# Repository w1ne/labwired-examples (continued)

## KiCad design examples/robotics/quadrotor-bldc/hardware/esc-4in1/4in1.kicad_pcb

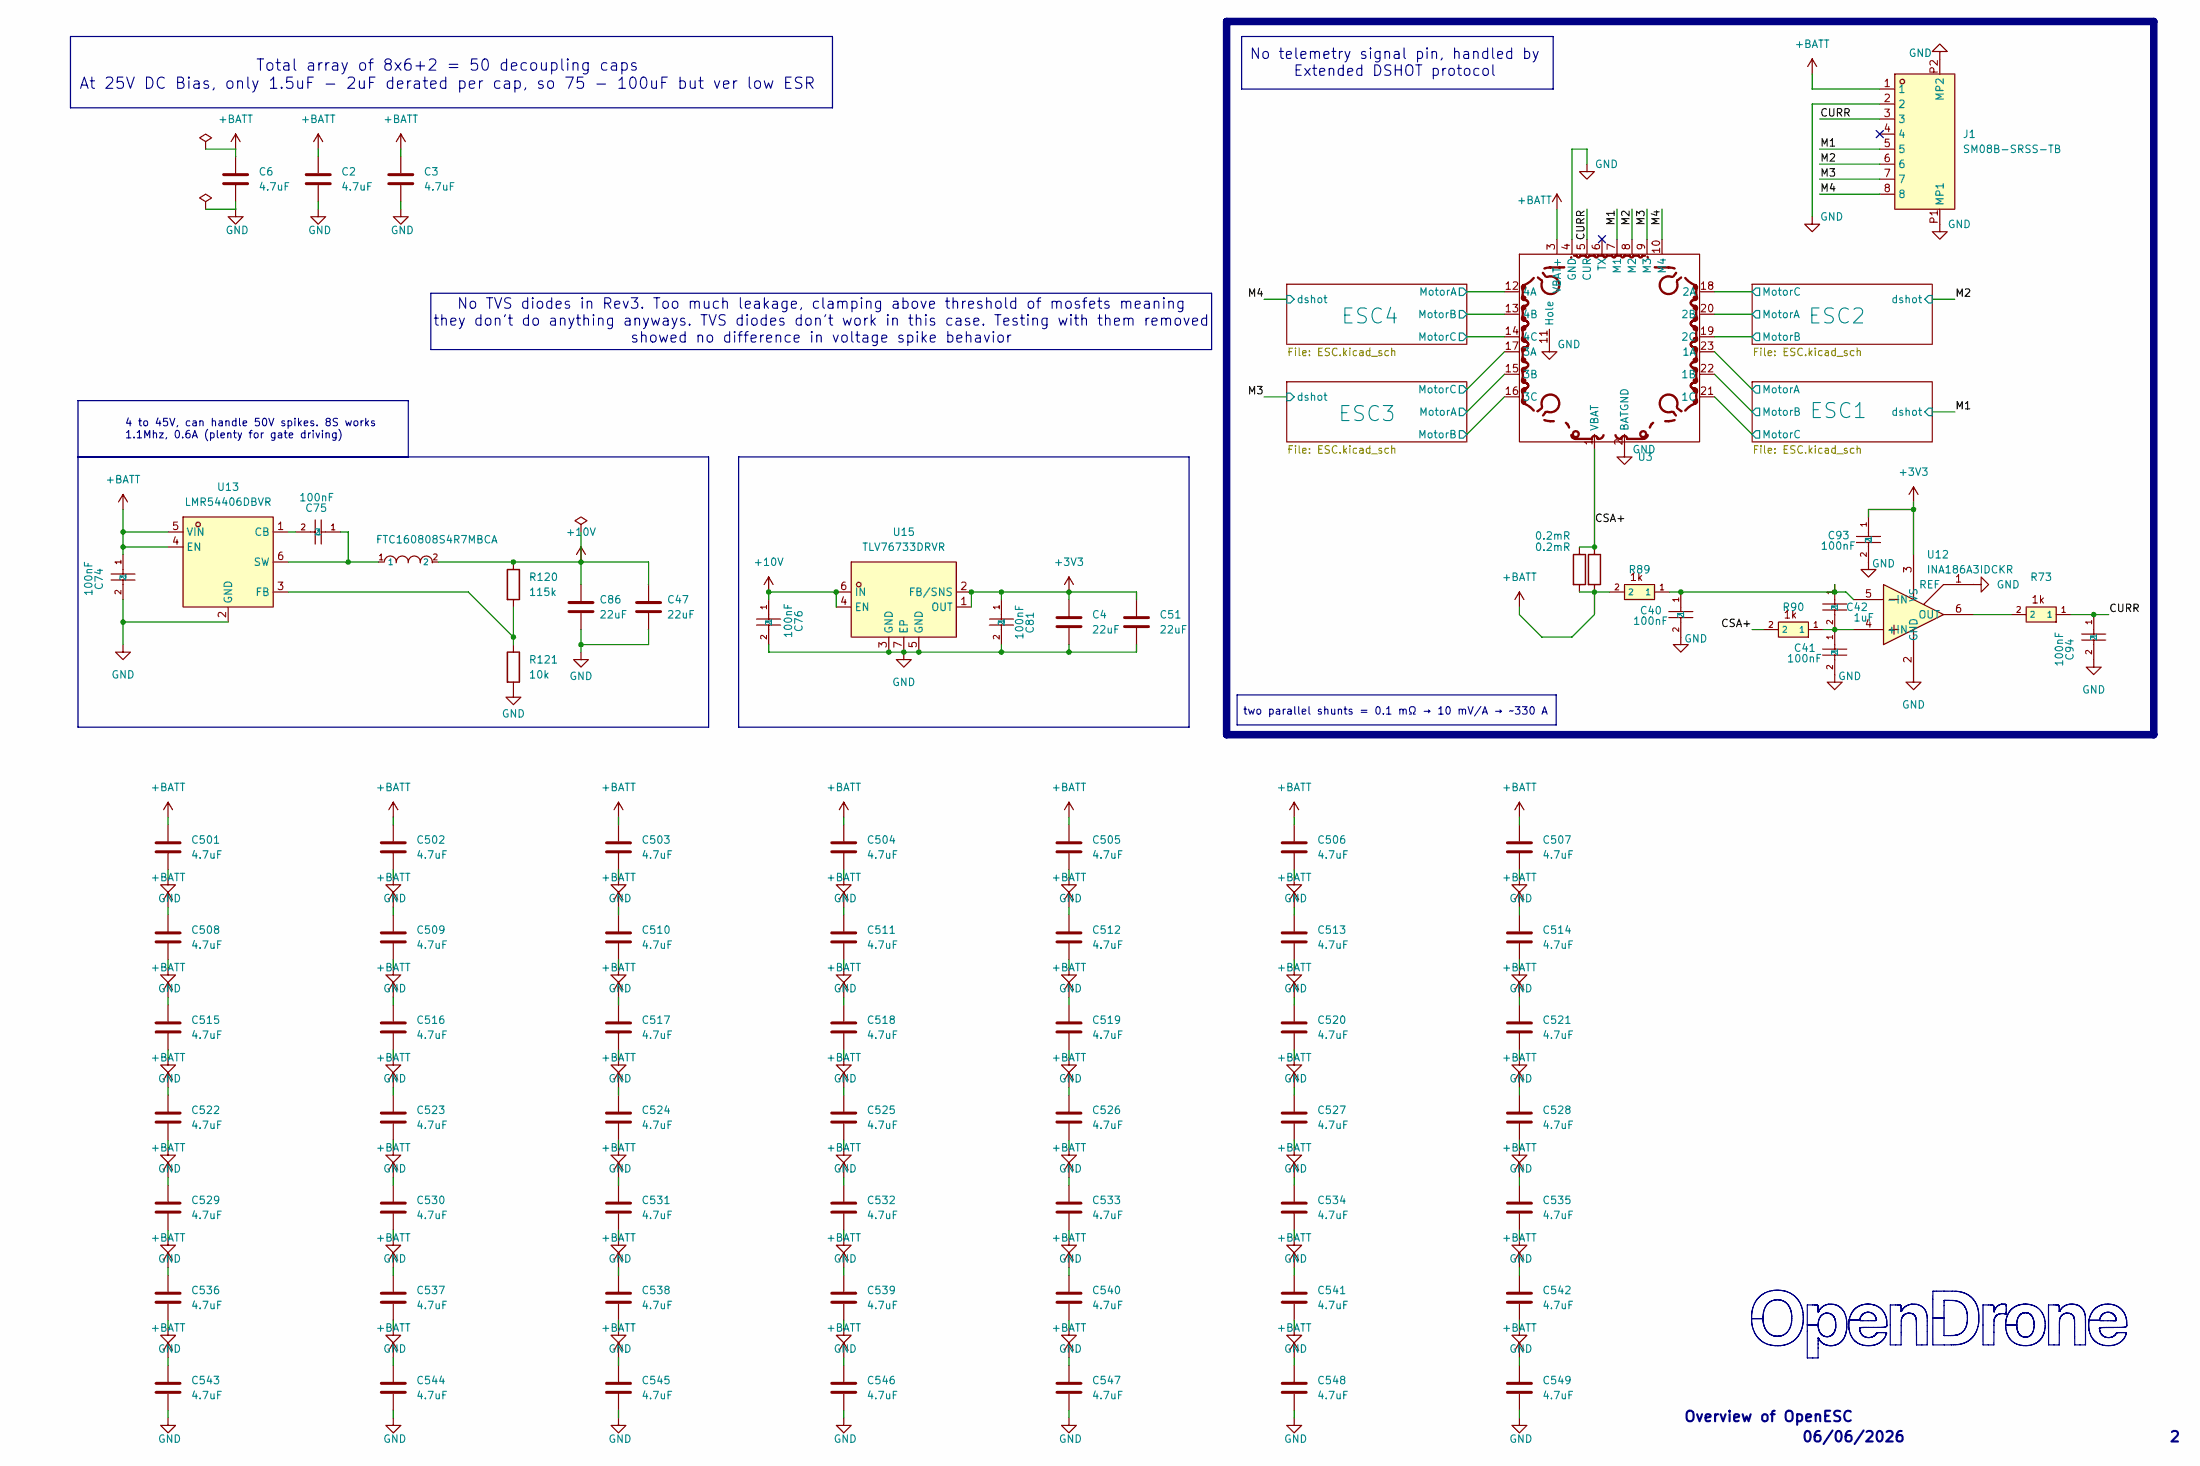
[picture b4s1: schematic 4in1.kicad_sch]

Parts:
C2, C3, C6, C501, C502, C503, C504, C505, C506, C507, C508, C509, C510, C511, C512, C513, C514, C515, C516, C517, C518, C519, C520, C521, C522, C523, C524, C525, C526, C527, C528, C529, C530, C531, C532, C533, C534, C535, C536, C537, C538, C539, C540, C541, C542, C543, C544, C545, C546, C547, C548, C549: 4.7uF; C_1206_3216Metric; MPN TCC1206X7R475K500HT; LCSC C380366
C4, C51: 22uF; C_0402_1005Metric; MPN CL05A226MQ5QUNC; LCSC C105226
C40, C41: 100nF; C_0402_WIDE; MPN CL05B104KB54PNC; LCSC C307331
C42: 1uF; C_0402_1005Metric; MPN CC0402KRX7R6BB105; LCSC C7500381
C47, C86: 22uF; C_0603_1608Metric; MPN CL10A226MO7JZNC; LCSC C2762594
C74, C75, C76, C81, C93, C94: 100nF; C_0201_0603Metric; MPN GRM033R6YA104KE14D; LCSC C181043
J1: SM08B-SRSS-TB; JST_SM08B-SRSS-TB; MPN SM08B-SRSS-TB(LF)(SN); LCSC C160407
R73, R89, R90: 1k; C_0201_0603Metric; MPN 0201WMF1001TEE; LCSC C270365
R120: 115k; R_0201_0603Metric; MPN RTT011153FTH; LCSC C166378
R121: 10k; R_0201_0603Metric; MPN RC0201FR-0710KL; LCSC C106225
Rsense1, Rsense2: 0.2mR; R_2512_6332Metric; MPN ASR-S-3-0.2F; LCSC C695806
U3: 4in1ESC30x30
U12: INA186A3IDCKR; SOT-363_SC-70-6; MPN INA186A3IDCKR; LCSC C2058245
U13: LMR54406DBVR; SOT-23-6_L2.9-W1.6-P0.95-LS2.8-BR; MPN LMR54406DBVR; LCSC Part C5219316
U14: FTC160808S4R7MBCA; IND-SMD_L1.6-W0.8_FTC160865SR47MBCA; MPN FTC160808S4R7MBCA; LCSC C46594347
U15: TLV76733DRVR; WSON-6_L2.0-W2.0-P0.65-TL-EP; MPN TLV76733DRVR; LCSC C2848334

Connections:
+3V3: C4.2, C51.2, C81.1, C93.1, U12.3 (VS), U15.1 (OUT), U15.2 (FB/SNS); also elsewhere on the board
+10V: C47.1, C76.1, C86.1, R120.1, U14.2, U15.4 (EN), U15.6 (IN); also elsewhere on the board
+BATT: C2.1, C3.1, C6.1, C74.1, C501.1, C502.1, C503.1, C504.1, C505.1, C506.1, C507.1, C508.1, C509.1, C510.1, C511.1, C512.1, C513.1, C514.1, C515.1, C516.1, C517.1, C518.1, C519.1, C520.1, C521.1, C522.1, C523.1, C524.1, C525.1, C526.1, C527.1, C528.1, C529.1, C530.1, C531.1, C532.1, C533.1, C534.1, C535.1, C536.1, C537.1, C538.1, C539.1, C540.1, C541.1, C542.1, C543.1, C544.1, C545.1, C546.1, C547.1, C548.1, C549.1, J1.1, R89.2, Rsense1.2, Rsense2.2, U3.3 (VBAT+), U13.4 (EN), U13.5 (VIN); also elsewhere on the board
/CSA+: R90.2, Rsense1.1, Rsense2.1, U3.1 (VBAT)
/CURR: C94.1, J1.3, R73.1, U3.5 (CUR)
/ESC1/MotorA: U3.23 (1A); also elsewhere on the board
/ESC1/MotorB: U3.22 (1B); also elsewhere on the board
/ESC1/MotorC: U3.21 (1C); also elsewhere on the board
/ESC2/MotorA: U3.20 (2B); also elsewhere on the board
/ESC2/MotorB: U3.19 (2C); also elsewhere on the board
/ESC2/MotorC: U3.18 (2A); also elsewhere on the board
/ESC3/MotorA: U3.15 (3B); also elsewhere on the board
/ESC3/MotorB: U3.16 (3C); also elsewhere on the board
/ESC3/MotorC: U3.17 (3A); also elsewhere on the board
/ESC4/MotorA: U3.12 (4A); also elsewhere on the board
/ESC4/MotorB: U3.13 (4B); also elsewhere on the board
/ESC4/MotorC: U3.14 (4C); also elsewhere on the board
/M1: J1.5, U3.7 (M1); also elsewhere on the board
/M2: J1.6, U3.8 (M2); also elsewhere on the board
/M3: J1.7, U3.9 (M3); also elsewhere on the board
/M4: J1.8, U3.10 (M4); also elsewhere on the board
GND: C2.2, C3.2, C4.1, C6.2, C40.2, C41.2, C47.2, C51.1, C74.2, C76.2, C81.2, C86.2, C93.2, C94.2, C501.2, C502.2, C503.2, C504.2, C505.2, C506.2, C507.2, C508.2, C509.2, C510.2, C511.2, C512.2, C513.2, C514.2, C515.2, C516.2, C517.2, C518.2, C519.2, C520.2, C521.2, C522.2, C523.2, C524.2, C525.2, C526.2, C527.2, C528.2, C529.2, C530.2, C531.2, C532.2, C533.2, C534.2, C535.2, C536.2, C537.2, C538.2, C539.2, C540.2, C541.2, C542.2, C543.2, C544.2, C545.2, C546.2, C547.2, C548.2, C549.2, J1.2, J1.P1 (MP1), J1.P2 (MP2), R121.2, U3.2 (BATGND), U3.4 (GND), U3.11 (Hole), U12.1 (REF), U12.2 (GND), U13.2 (GND), U15.3 (GND), U15.5 (GND), U15.7 (EP); also elsewhere on the board
unnamed: C41.1, C42.2, R90.1, U12.4 (+IN)
unnamed: C40.1, C42.1, R89.1, U12.5 (-IN)
unnamed: R73.2, U12.6 (OUT)
unnamed: C75.2, U13.1 (CB)
unnamed: R120.2, R121.1, U13.3 (FB)
unnamed: C75.1, U13.6 (SW), U14.1

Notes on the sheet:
No telemetry signal pin, handled by Extended DSHOT protocol
Overview of OpenESC
No TVS diodes in Rev3. Too much leakage, clamping above threshold of mosfets meaning they don't do anything anyways. TVS diodes don't work in this case. Testing with them removed showed no difference in voltage spike behavior
06/06/2026
Total array of 8x6+2 = 50 decoupling caps At 25V DC Bias, only 1.5uF - 2uF derated per cap, so 75 - 100uF but ver low ESR
two parallel shunts = 0.1 mΩ → 10 mV/A → ~330 A
4 to 45V, can handle 50V spikes. 8S works 1.1Mhz, 0.6A (plenty for gate driving)

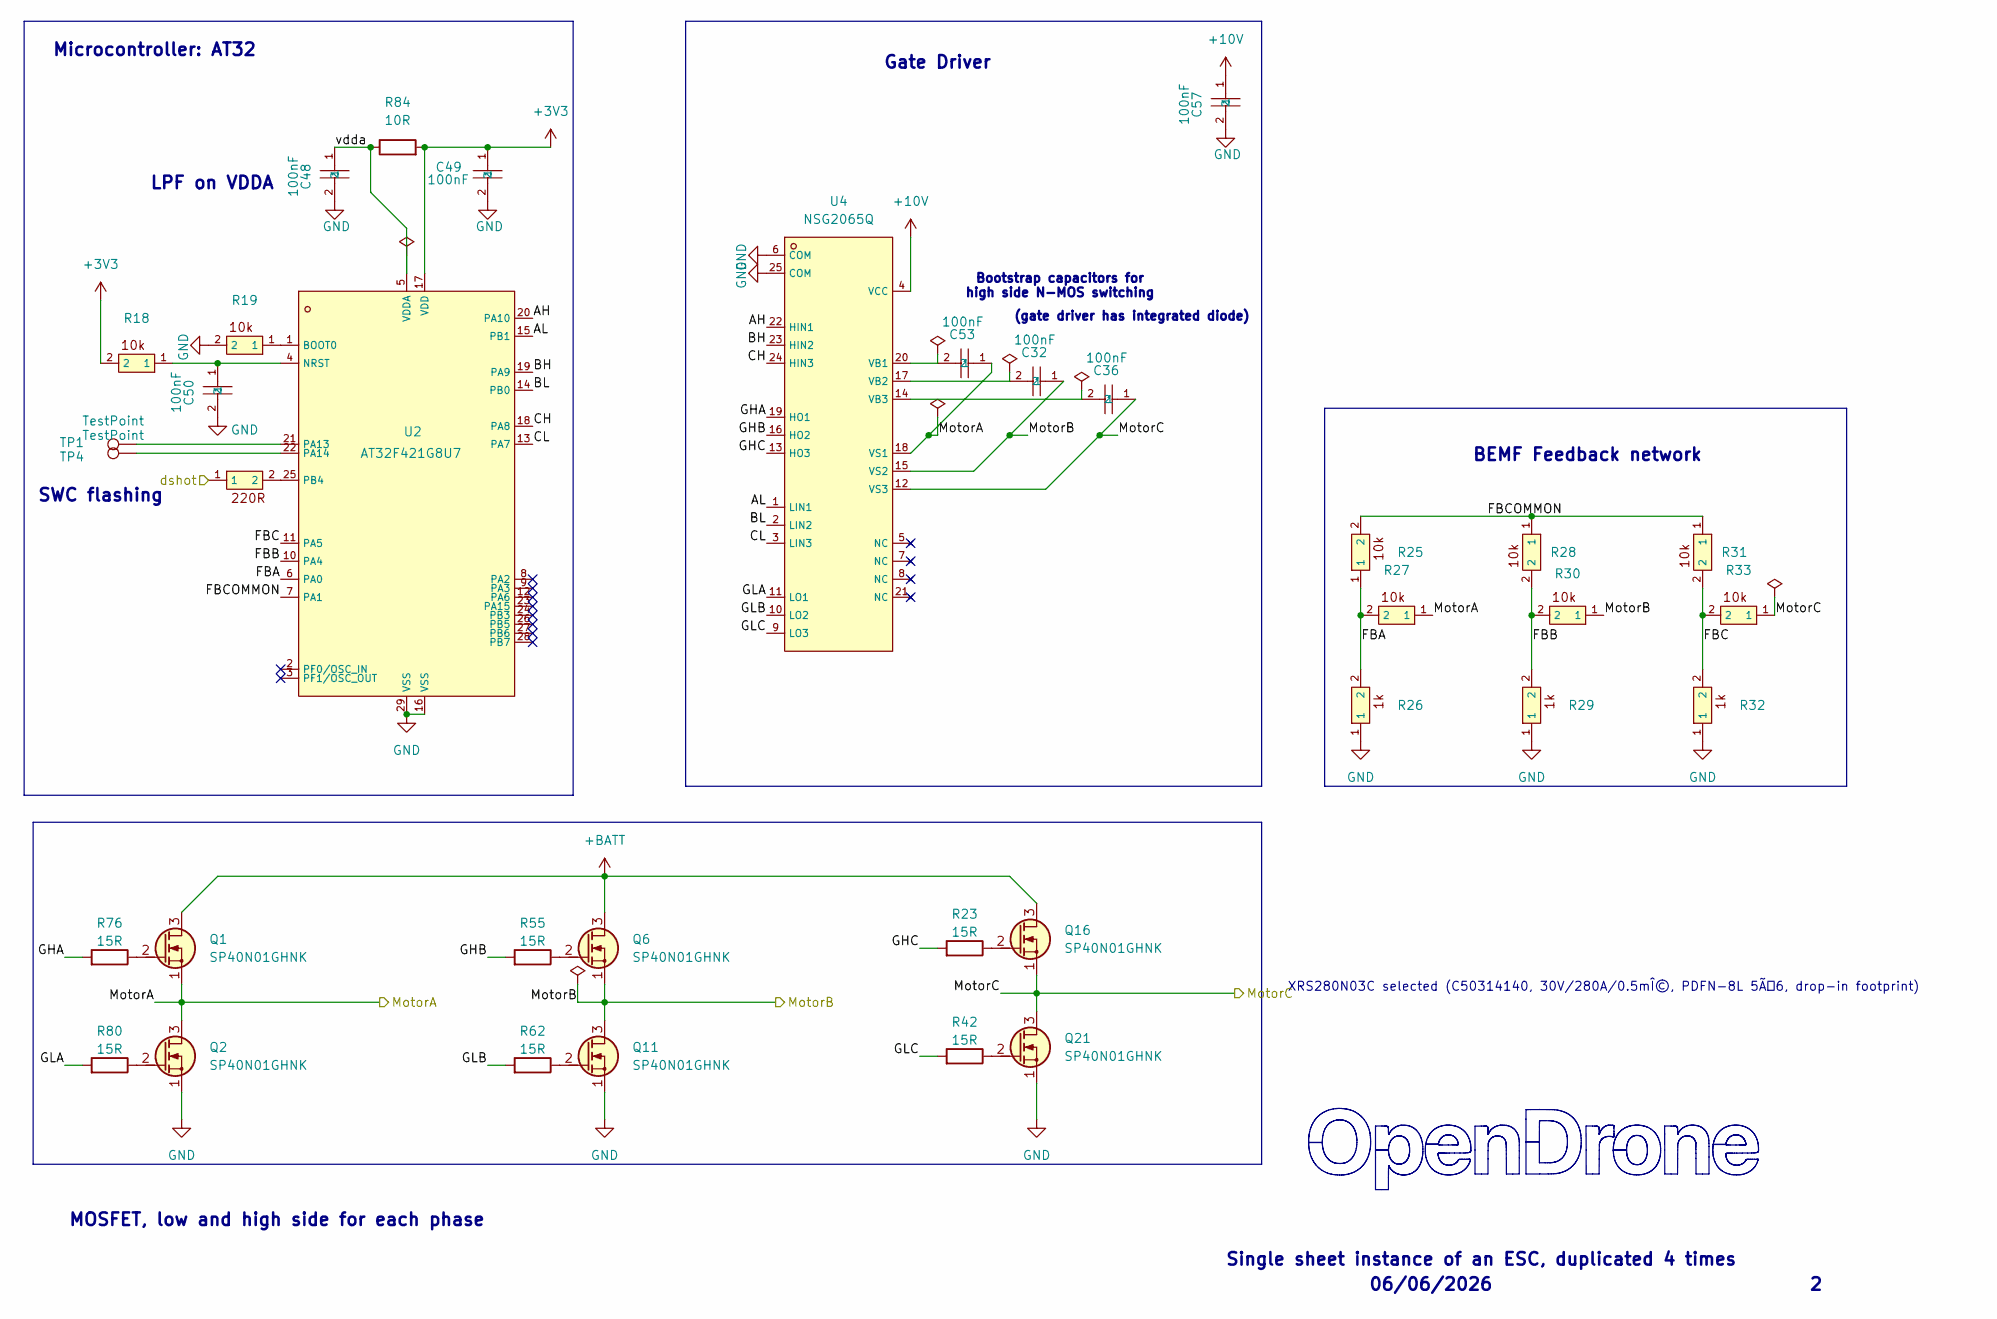
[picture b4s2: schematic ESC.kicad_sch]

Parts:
C32, C36, C53: 100nF; C_0402_WIDE; MPN CL05B104KB54PNC; LCSC C307331
C48, C49, C50, C57: 100nF; C_0201_0603Metric; MPN GRM033R6YA104KE14D; LCSC C181043
Q1, Q2, Q6, Q11, Q16, Q21: SP40N01GHNK; PDFN-8L_L6.0-W5.0-P1.27; MPN SP40N01GHNK; LCSC C22385416
R18, R19: 10k; R_0201_0603Metric; MPN RC0201FR-0710KL; LCSC C106225
R20: 220R; R_0201_0603Metric; MPN AC0201FR-07220RL; LCSC C226468
R23, R42, R55, R62, R76, R80: 15R; R_0201_0603Metric; MPN 0201WMF150JTEE; LCSC C473542
R25, R27, R28, R30, R31, R33: 10k; C_0201_0603Metric; MPN RC0201FR-0710KL; LCSC C106225
R26, R29, R32: 1k; C_0201_0603Metric; MPN 0201WMF1001TEE; LCSC C270365
R84: 10R; R_0201_0603Metric; MPN RC0201FR-0710RL; LCSC C106226
TP1, TP4: TestPoint; TestPoint_Pad_D1.0mm
U2: AT32F421G8U7; QFN-28_L4.0-W4.0-P0.40-TL-EP2.4; MPN AT32F421G8U7; LCSC C2765098
U4: NSG2065Q; QFN-24_L4.0-W4.0-P0.50-TL-EP2.8; MPN NSG2065Q; LCSC C41414478

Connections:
+3V3: C49.1, R18.2, R84.2, U2.17 (VDD); also elsewhere on the board
+10V: C57.1, U4.4 (VCC); also elsewhere on the board
+BATT: Q1.3 (D), Q6.3 (D), Q16.3 (D); also elsewhere on the board
/ESC1/AH: U2.20 (PA10), U4.22 (HIN1)
/ESC1/AL: U2.15 (PB1), U4.1 (LIN1)
/ESC1/BH: U2.19 (PA9), U4.23 (HIN2)
/ESC1/BL: U2.14 (PB0), U4.2 (LIN2)
/ESC1/CH: U2.18 (PA8), U4.24 (HIN3)
/ESC1/CL: U2.13 (PA7), U4.3 (LIN3)
/ESC1/FBA: R25.1, R26.2, R27.2, U2.6 (PA0)
/ESC1/FBB: R28.2, R29.2, R30.2, U2.10 (PA4)
/ESC1/FBC: R31.2, R32.2, R33.2, U2.11 (PA5)
/ESC1/FBCOMMON: R25.2, R28.1, R31.1, U2.7 (PA1)
/ESC1/GHA: R76.1, U4.19 (HO1)
/ESC1/GHB: R55.1, U4.16 (HO2)
/ESC1/GHC: R23.1, U4.13 (HO3)
/ESC1/GLA: R80.1, U4.11 (LO1)
/ESC1/GLB: R62.1, U4.10 (LO2)
/ESC1/GLC: R42.1, U4.9 (LO3)
/ESC1/MotorA: C53.1, Q1.1 (S), Q2.3 (D), R27.1, U4.18 (VS1); also elsewhere on the board
/ESC1/MotorB: C32.1, Q6.1 (S), Q11.3 (D), R30.1, U4.15 (VS2); also elsewhere on the board
/ESC1/MotorC: C36.1, Q16.1 (S), Q21.3 (D), R33.1, U4.12 (VS3); also elsewhere on the board
/ESC1/vdda: C48.1, R84.1, U2.5 (VDDA)
/M1: R20.1; also elsewhere on the board
GND: C48.2, C49.2, C50.2, C57.2, Q2.1 (S), Q11.1 (S), Q21.1 (S), R19.2, R26.1, R29.1, R32.1, U2.16 (VSS), U2.29 (VSS), U4.6 (COM), U4.25 (COM); also elsewhere on the board
unnamed: Q1.2 (G), R76.2
unnamed: Q2.2 (G), R80.2
unnamed: Q6.2 (G), R55.2
unnamed: Q11.2 (G), R62.2
unnamed: Q16.2 (G), R23.2
unnamed: Q21.2 (G), R42.2
unnamed: R19.1, U2.1 (BOOT0)
unnamed: C50.1, R18.1, U2.4 (NRST)
unnamed: TP1.1 (1_1), U2.21 (PA13)
unnamed: TP4.1 (1_1), U2.22 (PA14)
unnamed: R20.2, U2.25 (PB4)
unnamed: C53.2, U4.20 (VB1)
unnamed: C32.2, U4.17 (VB2)
unnamed: C36.2, U4.14 (VB3)

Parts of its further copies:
C33, C34, C35, C37, C38, C39, C56, C62, C67: 100nF; C_0402_WIDE; MPN CL05B104KB54PNC; LCSC C307331
C52, C54, C55, C58, C59, C60, C61, C63, C64, C65, C66, C68: 100nF; C_0201_0603Metric; MPN GRM033R6YA104KE14D; LCSC C181043
Q3, Q4, Q5, Q7, Q8, Q9, Q10, Q12, Q13, Q14, Q15, Q17, Q18, Q19, Q20, Q22, Q23, Q24: SP40N01GHNK; PDFN-8L_L6.0-W5.0-P1.27; MPN SP40N01GHNK; LCSC C22385416
R10, R12, R13, R15, R34, R36, R46, R48, R49, R51, R52, R54, R64, R66, R67, R69, R70, R72: 10k; C_0201_0603Metric; MPN RC0201FR-0710KL; LCSC C106225
R11, R14, R35, R47, R50, R53, R65, R68, R71: 1k; C_0201_0603Metric; MPN 0201WMF1001TEE; LCSC C270365
R21, R22, R40, R41, R58, R59: 10k; R_0201_0603Metric; MPN RC0201FR-0710KL; LCSC C106225
R24, R37, R38, R43, R44, R45, R56, R60, R61, R63, R74, R75, R77, R78, R79, R81, R82, R83: 15R; R_0201_0603Metric; MPN 0201WMF150JTEE; LCSC C473542
R39, R57, R87: 220R; R_0201_0603Metric; MPN AC0201FR-07220RL; LCSC C226468
R85, R86, R88: 10R; R_0201_0603Metric; MPN RC0201FR-0710RL; LCSC C106226
TP2, TP3, TP5, TP6, TP7, TP8: TestPoint; TestPoint_Pad_D1.0mm
U5, U7, U9: AT32F421G8U7; QFN-28_L4.0-W4.0-P0.40-TL-EP2.4; MPN AT32F421G8U7; LCSC C2765098
U6, U8, U10: NSG2065Q; QFN-24_L4.0-W4.0-P0.50-TL-EP2.8; MPN NSG2065Q; LCSC C41414478

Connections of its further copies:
+3V3: C55.1, C61.1, C66.1, R21.2, R40.2, R58.2, R85.2, R86.2, R88.2, U5.17 (VDD), U7.17 (VDD), U9.17 (VDD); also elsewhere on the board
+10V: C58.1, C63.1, C68.1, U6.4 (VCC), U8.4 (VCC), U10.4 (VCC); also elsewhere on the board
+BATT: Q7.3 (D), Q8.3 (D), Q9.3 (D), Q10.3 (D), Q13.3 (D), Q17.3 (D), Q18.3 (D), Q19.3 (D), Q20.3 (D); also elsewhere on the board
/ESC2/AH: U5.20 (PA10), U6.22 (HIN1)
/ESC2/AL: U5.15 (PB1), U6.1 (LIN1)
/ESC2/BH: U5.19 (PA9), U6.23 (HIN2)
/ESC2/BL: U5.14 (PB0), U6.2 (LIN2)
/ESC2/CH: U5.18 (PA8), U6.24 (HIN3)
/ESC2/CL: U5.13 (PA7), U6.3 (LIN3)
/ESC2/FBA: R10.1, R11.2, R12.2, U5.6 (PA0)
/ESC2/FBB: R13.2, R14.2, R15.2, U5.10 (PA4)
/ESC2/FBC: R34.2, R35.2, R36.2, U5.11 (PA5)
/ESC2/FBCOMMON: R10.2, R13.1, R34.1, U5.7 (PA1)
/ESC2/GHA: R77.1, U6.19 (HO1)
/ESC2/GHB: R56.1, U6.16 (HO2)
/ESC2/GHC: R24.1, U6.13 (HO3)
/ESC2/GLA: R81.1, U6.11 (LO1)
/ESC2/GLB: R63.1, U6.10 (LO2)
/ESC2/GLC: R43.1, U6.9 (LO3)
/ESC2/MotorA: C56.1, Q3.3 (D), Q7.1 (S), R12.1, U6.18 (VS1); also elsewhere on the board
/ESC2/MotorB: C33.1, Q8.1 (S), Q12.3 (D), R15.1, U6.15 (VS2); also elsewhere on the board
/ESC2/MotorC: C37.1, Q17.1 (S), Q22.3 (D), R36.1, U6.12 (VS3); also elsewhere on the board
/ESC2/vdda: C54.1, R85.1, U5.5 (VDDA)
/ESC3/AH: U7.20 (PA10), U8.22 (HIN1)
/ESC3/AL: U7.15 (PB1), U8.1 (LIN1)
/ESC3/BH: U7.19 (PA9), U8.23 (HIN2)
/ESC3/BL: U7.14 (PB0), U8.2 (LIN2)
/ESC3/CH: U7.18 (PA8), U8.24 (HIN3)
/ESC3/CL: U7.13 (PA7), U8.3 (LIN3)
/ESC3/FBA: R46.1, R47.2, R48.2, U7.6 (PA0)
/ESC3/FBB: R49.2, R50.2, R51.2, U7.10 (PA4)
/ESC3/FBC: R52.2, R53.2, R54.2, U7.11 (PA5)
/ESC3/FBCOMMON: R46.2, R49.1, R52.1, U7.7 (PA1)
/ESC3/GHA: R78.1, U8.19 (HO1)
/ESC3/GHB: R60.1, U8.16 (HO2)
/ESC3/GHC: R37.1, U8.13 (HO3)
/ESC3/GLA: R82.1, U8.11 (LO1)
/ESC3/GLB: R74.1, U8.10 (LO2)
/ESC3/GLC: R44.1, U8.9 (LO3)
/ESC3/MotorA: C62.1, Q4.3 (D), Q13.1 (S), R48.1, U8.18 (VS1); also elsewhere on the board
/ESC3/MotorB: C34.1, Q9.1 (S), Q14.3 (D), R51.1, U8.15 (VS2); also elsewhere on the board
/ESC3/MotorC: C38.1, Q18.1 (S), Q23.3 (D), R54.1, U8.12 (VS3); also elsewhere on the board
/ESC3/vdda: C60.1, R86.1, U7.5 (VDDA)
/ESC4/AH: U9.20 (PA10), U10.22 (HIN1)
/ESC4/AL: U9.15 (PB1), U10.1 (LIN1)
/ESC4/BH: U9.19 (PA9), U10.23 (HIN2)
/ESC4/BL: U9.14 (PB0), U10.2 (LIN2)
/ESC4/CH: U9.18 (PA8), U10.24 (HIN3)
/ESC4/CL: U9.13 (PA7), U10.3 (LIN3)
/ESC4/FBA: R64.1, R65.2, R66.2, U9.6 (PA0)
/ESC4/FBB: R67.2, R68.2, R69.2, U9.10 (PA4)
/ESC4/FBC: R70.2, R71.2, R72.2, U9.11 (PA5)
/ESC4/FBCOMMON: R64.2, R67.1, R70.1, U9.7 (PA1)
/ESC4/GHA: R79.1, U10.19 (HO1)
/ESC4/GHB: R61.1, U10.16 (HO2)
/ESC4/GHC: R38.1, U10.13 (HO3)
/ESC4/GLA: R83.1, U10.11 (LO1)
/ESC4/GLB: R75.1, U10.10 (LO2)
/ESC4/GLC: R45.1, U10.9 (LO3)
/ESC4/MotorA: C67.1, Q5.3 (D), Q19.1 (S), R66.1, U10.18 (VS1); also elsewhere on the board
/ESC4/MotorB: C35.1, Q10.1 (S), Q15.3 (D), R69.1, U10.15 (VS2); also elsewhere on the board
/ESC4/MotorC: C39.1, Q20.1 (S), Q24.3 (D), R72.1, U10.12 (VS3); also elsewhere on the board
/ESC4/vdda: C65.1, R88.1, U9.5 (VDDA)
/M2: R39.1; also elsewhere on the board
/M3: R57.1; also elsewhere on the board
/M4: R87.1; also elsewhere on the board
GND: C52.2, C54.2, C55.2, C58.2, C59.2, C60.2, C61.2, C63.2, C64.2, C65.2, C66.2, C68.2, Q3.1 (S), Q4.1 (S), Q5.1 (S), Q12.1 (S), Q14.1 (S), Q15.1 (S), Q22.1 (S), Q23.1 (S), Q24.1 (S), R11.1, R14.1, R22.2, R35.1, R41.2, R47.1, R50.1, R53.1, R59.2, R65.1, R68.1, R71.1, U5.16 (VSS), U5.29 (VSS), U6.6 (COM), U6.25 (COM), U7.16 (VSS), U7.29 (VSS), U8.6 (COM), U8.25 (COM), U9.16 (VSS), U9.29 (VSS), U10.6 (COM), U10.25 (COM); also elsewhere on the board
unnamed: Q3.2 (G), R81.2
unnamed: Q4.2 (G), R82.2
unnamed: Q5.2 (G), R83.2
unnamed: Q7.2 (G), R77.2
unnamed: Q8.2 (G), R56.2
unnamed: Q9.2 (G), R60.2
unnamed: Q10.2 (G), R61.2
unnamed: Q12.2 (G), R63.2
unnamed: Q13.2 (G), R78.2
unnamed: Q14.2 (G), R74.2
unnamed: Q15.2 (G), R75.2
unnamed: Q17.2 (G), R24.2
unnamed: Q18.2 (G), R37.2
unnamed: Q19.2 (G), R79.2
unnamed: Q20.2 (G), R38.2
unnamed: Q22.2 (G), R43.2
unnamed: Q23.2 (G), R44.2
unnamed: Q24.2 (G), R45.2
unnamed: R22.1, U5.1 (BOOT0)
unnamed: C52.1, R21.1, U5.4 (NRST)
unnamed: TP2.1 (1_1), U5.21 (PA13)
unnamed: TP5.1 (1_1), U5.22 (PA14)
unnamed: R39.2, U5.25 (PB4)
unnamed: C56.2, U6.20 (VB1)
unnamed: C33.2, U6.17 (VB2)
unnamed: C37.2, U6.14 (VB3)
unnamed: R41.1, U7.1 (BOOT0)
unnamed: C59.1, R40.1, U7.4 (NRST)
unnamed: TP3.1 (1_1), U7.21 (PA13)
unnamed: TP6.1 (1_1), U7.22 (PA14)
unnamed: R57.2, U7.25 (PB4)
unnamed: C62.2, U8.20 (VB1)
unnamed: C34.2, U8.17 (VB2)
unnamed: C38.2, U8.14 (VB3)
unnamed: R59.1, U9.1 (BOOT0)
unnamed: C64.1, R58.1, U9.4 (NRST)
unnamed: TP7.1 (1_1), U9.21 (PA13)
unnamed: TP8.1 (1_1), U9.22 (PA14)
unnamed: R87.2, U9.25 (PB4)
unnamed: C67.2, U10.20 (VB1)
unnamed: C35.2, U10.17 (VB2)
unnamed: C39.2, U10.14 (VB3)

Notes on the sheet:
Single sheet instance of an ESC, duplicated 4 times
MOSFET, low and high side for each phase
Gate Driver
SWC flashing
XRS280N03C selected (C50314140, 30V/280A/0.5mÎ©, PDFN-8L 5Ã6, drop-in footprint)
Bootstrap capacitors for high side N-MOS switching
BEMF Feedback network
(gate driver has integrated diode)
Microcontroller: AT32
LPF on VDDA
06/06/2026

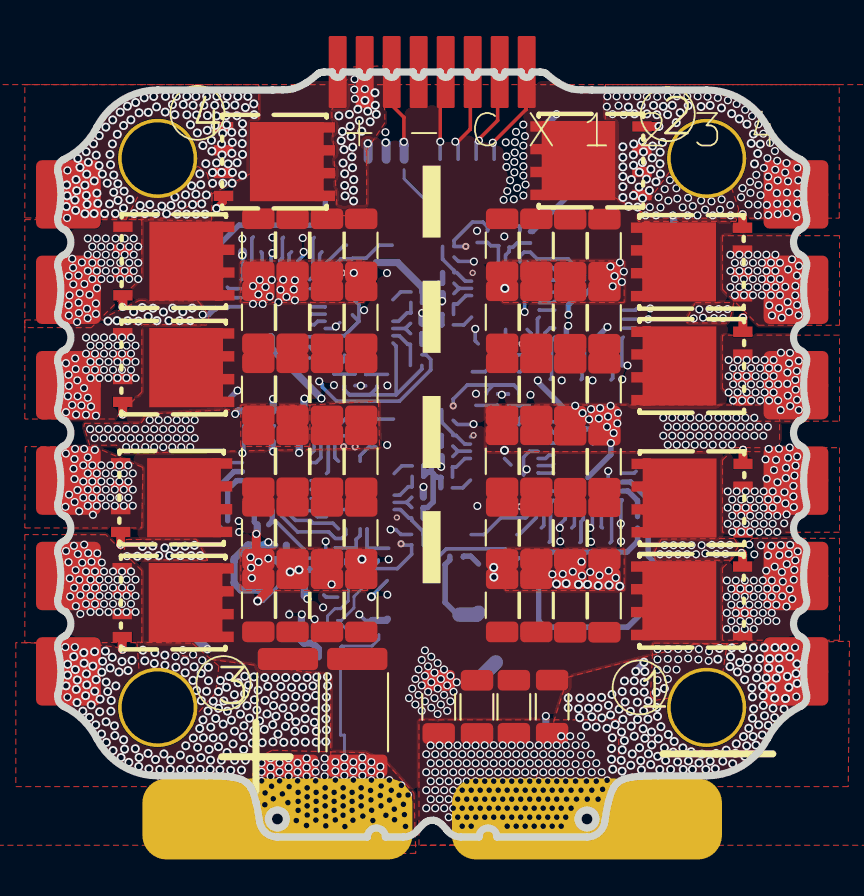
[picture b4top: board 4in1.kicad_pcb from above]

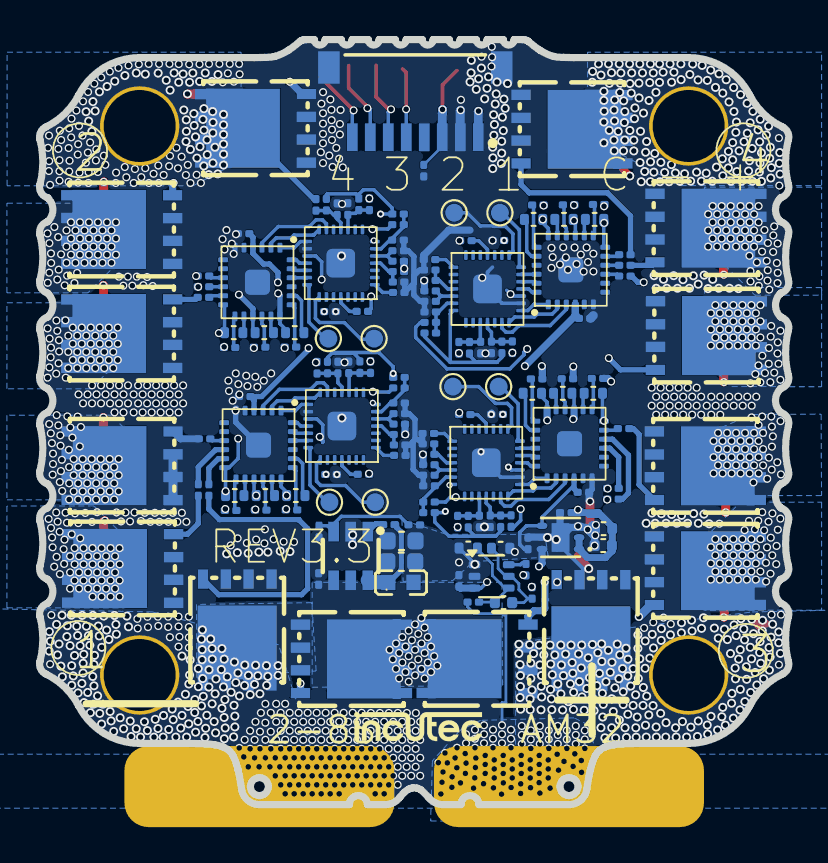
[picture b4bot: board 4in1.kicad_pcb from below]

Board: 6 copper layers, 41.6 x 42.5 mm, 222 parts (157 on the bottom side), 152 nets.

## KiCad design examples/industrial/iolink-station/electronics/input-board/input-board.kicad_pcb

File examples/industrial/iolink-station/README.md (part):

# Two-port STM32L476 IO-Link input station

This package retains the published station's three **NUCLEO-L476RG** controllers
and two independent device ports. It provides physical ST HAL firmware, two
L6360 master interfaces, two L6362A device interfaces, and a native routed
eight-input PCB for each device. The physical firmware supports **COM2,
38,400 bit/s, 8 data bits, even parity, one stop bit**, with one input process
byte per device, TYPE_2_1 M-sequences and a 10 ms configured cycle.

**Release state:** electrical and firmware runtime candidate. Both physical
images build, and the unchanged master plus both unchanged device images
pass a complete digital station run: two OPERATE ports, independent input
patterns and input changes, with zero PHY/UART/overflow/wire errors. The
native input PCB has zero ERC, DRC, unconnected-net and schematic-parity
findings. A complete fitted station mount, physical power/waveform
measurements and a two-port hardware acceptance run remain required. The
L6360 stored-parity startup repair passes 18 host tests. See the
[exact three-node runtime proof and reproduction command](runtime/README.md).

## Contents and evidence

| Item | Files | Evidence |
|---|---|---|
| Physical master | `firmware/master/`, `firmware/common/` | ST HAL, real I2C L6360 transactions, timer-generated wake-up and two UARTs |
| Physical input devices | `firmware/device/` | L6362A control, overload wake-up, inverted UART interface and HC165 input scan |
| Editable input electronics | `electronics/input-board/` | KiCad 10 project, schematic, PCB and local libraries |
| Fabrication and assembly | `manufacturing/input-board/` | Copper/mask/silkscreen/paste/outline Gerbers, drill, DSN/SES, netlist and schematic PDF |
| Native board geometry | `cad/input-board-populated.step`, `cad/input-board-substrate.step` | KiCad exports; populated render in `cad/input-board-iso.png` |
| Parts and wiring | `hardware/station-bom.csv`, `hardware/input-board-bom.csv`, pin-map and harness JSON | Exact purchased board, PHY routing, connector and passive identities |
| Build and checks | `evidence/` | Source/binary hashes, build logs, host tests, timing calculation, native ERC/DRC and visual review |
| Purchased routed boards | `hardware/vendor-sources.json`, `hardware/fetch-vendor.py` | Exact official ST schematic/BOM/manufacturing archive hashes |

J2 now uses a **TSW-108-07-G-D drawing-derived clearance envelope** instead
of the taller generic KiCad pin header. Its 10.92 mm overall length comprises
a 2.54 mm tail, 2.54 mm body and 5.84 mm post; pins are 0.635 mm square.
The source and nominal/tolerance limits are retained under
`mechanical/references/`. This is an explicitly labeled envelope, not a
manufacturer solid or a measured as-built connector. The native board
remains 14 valid solids, with substrate index 13 and header index 4.

The ST shields are purchased populated boards. Their official manufacturing
archives establish routed-board provenance; they do not make the shield CAD
editable in KiCad. The input PCB is fully editable in this repository.
The common MB1136 Altium design is a Nucleo geometry reference, not a claim
that a generic board BOM reproduces every NUCLEO-L476RG variant.

## Hardware and power

Use one NUCLEO-L476RG with **two STEVAL-IOM001V1** shields for the master.
Use one NUCLEO-L476RG, one **STEVAL-IOD003V1**, and one input PCB for each
device. Keep the ST-LINK section of all three Nucleos attached and USB powered.

The selected field supply is **Mean Well GST25A24-P1J**, 24 V, 1.04 A,
with a centre-positive 2.1 × 5.5 mm output. Connect its plug to an
**Adafruit 368** female terminal adapter. Use separate **WAGO 221-413**
three-way splices for +24 V and return, with one wire per clamp. Feed both
master shields: **CN1.3 = +24 V; CN1.1 = GND**. Leave CN1.2 and the
alternative 7–12 V input CN2 unused. Set SW6 to pins 2–3.

Each three-wire field cable connects a master's **CN3** to the corresponding
device shield's **CN1**: pin **1 = L+**, **3 = GND**, **4 = C/Q**.
Pins 2 and 5 are unused for this Type A package. The exact cable cuts,
colours and terminations are in `hardware/harnesses.json`.
These are screw-terminal bench cables, not an M12 connector assembly.

Supply the Nucleo logic through the three USB/ST-LINK connectors, with each
Nucleo JP5 at **U5V**. On each IOD shield, leave **JP3, JP4 and JP5 open**:
the L6362A generated rails must not backfeed the USB-powered Nucleo rails.
Keep JP1 closed and JP2/JP6 open. A region-approved IEC C13 mains lead for
the selected Class I supply is required; its regional plug part number is
not selected by this package.

Disconnect USB and 24 V before solder-bridge or resistor changes. Identify
connector pin 1 from the board marking and the vendor drawing before wiring.
Check continuity and absence of rail shorts before applying power. This
open bench station does not claim an industrial enclosure, ingress rating,
EMC qualification or galvanic isolation.

## Required Nucleo clock configuration

On **all three** NUCLEO-L476RG boards set **SB16, SB50 and SB54 ON**;
set **SB55 OFF** and leave **R35/R37 not fitted**. UM1724 §7.9.1 documents
the retained ST-LINK's 8 MHz MCO into PH0/HSE. Firmware uses HSE bypass and
PLL /2 ×40 /2 for an 80 MHz CPU/peripheral clock. It fails initialization if
this source is unavailable.

At nominal 80 MHz, the UART divider gives **38,406.145 bit/s**, a
**+160.026 ppm** divider error. The physical C/Q rate remains unmeasured.
The L476 MSI automatic-trim specification is wider than the IO-Link master
±0.1% rate requirement, so the physical target does not use MSI as its
communication clock. The ±5% sweep in the analytical timing receipt is a
margin exercise for the I2C/wake calculation, not an allowed UART frequency
error or a measured oscillator specification.

## Master rework and pin map

Both IOM shields share I2C1: **PB8 AF4 / CN10.3 = SCL** and
**PB9 AF4 / CN10.5 = SDA**. Keep the factory pull-up connections JP2/JP3.
The two local PHY pull-up networks and their routing resistors remain on
the purchased shields; do not add a hard connection between their local VDD
outputs and the Nucleo 3.3 V rail.

| Signal | Port 1: default shield | Port 2: reconfigured shield |
|---|---|---|
| INCQ / transmit | PA9, USART1 AF7, CN10.21, R5 | PA0, UART4 AF8, CN7.28, R115 |
| OUTCQ / receive | PA10, USART1 AF7, CN10.33, R9 | PA1, UART4 AF8, CN7.30, R119 |
| ENCQ | PC0, CN7.38, R3 | PA5, CN10.11, R143 |
| ENL+ | PA6, CN10.13, R4 | PA8, CN10.23, R114 |
| Active-low reset | PB5, CN10.29, R8 | PC1, CN7.36, R108 |
| Active-low IRQ | PA4, CN7.32, R7 | PB0, CN7.34, R117 |
| IPS161H L+ ON | PB4, CN10.27, R162 | PA7, CN10.15, R163 |
| SA2/SA1/SA0 | 000 | 001 |
| Seven-bit I2C / HAL argument | 0x60 / 0xC0 | 0x61 / 0xC2 |

On the second shield remove the seven default routing resistors in the
port 1 column and fit the seven port 2 positions. Use **ERJ3BD1000V,
100 Ω, 0.5%, 0.1 W, 0603**, as identified in the official shield BOM.
Do not substitute zero-ohm links.

SW0/SW1/SW2 select SA0/SA1/SA2; pins 1–2 select ground and pins 2–3 select
VDD. Set all three to 1–2 on port 1; set SW0 to 2–3 and SW1/SW2 to 1–2
on port 2. UM2414's 0/1 address values describe the selectable suffix;
DS8900 §6.8 supplies the fixed 1100 prefix.

On both IOM shields set **SW3 2–3** for 3.3 V logic, **SW4/SW5 1–2**
for MCU enable control, **SW6 2–3** for the CN1 supply and **SW7 1–2**
for Type A. Retain factory J1/J2 routing. Firmware holds the auxiliary
IPS161H enable low; it uses the L6360 L+ path.

On the master Nucleo set **SB56/SB51 ON** and **SB46/SB52 OFF**, preserving
PC1/PC0 on A4/A5 for port 2 reset and port 1 ENCQ. Keep **SB13/SB14 ON**
and **SB62/SB63 OFF** for the existing ST-LINK USART2 routing. Optional
OUTIQ routing is not used.

## Device rework and input harness

On each IOD shield remove **R102** and fit **R112** to hold IN1 at ground.
Remove **R101** and fit **R111** to route IN2 to PA9/USART1 TX. Retain
R103 for OUTIQ/PA10, R109 for EN/PC7, R105 for OL/PA6 and R104 for
DIAG/PA4. Use the same 100 Ω routing part stated above. This requires
four additional resistors for the two devices, giving eleven for the
station's complete rework.

Close all three positions of SW1; retain SW2/SW3 at pins 2–3. The firmware
uses L6362A push-pull signalling, the hardware overload input for physical
wake-up, and **TXINV/RXINV** on USART1 for the resulting logic polarity.
It does not replace wake-up with a UART 0x55 byte.

The six-pin input PCB connector **J1** connects to the Nucleo Morpho
underside. Fit the mating XHP-6 shell with SXH-001T-P0.6 contacts; terminate
the Nucleo ends with four M20-1060100 single shells, one M20-1060200
two-position shell, and six M20-1180042 contacts per device. Put CN10.28
(QH, white) and CN10.30 (CLK, blue) in the shared two-position shell; this
avoids interference between adjacent single housings. Harwin specifies
5.50–6.30 mm mating pin length. Use the mount's controlled insertion stop;
do not force a housing flush against a longer underside header tail.

| Input PCB J1 | Signal | NUCLEO-L476RG |
|---|---|---|
| 1 | GND | CN7.20 |
| 2 | +3.3 V | CN7.16 |
| 3 | HC165 clock | PB13 / CN10.30 |
| 4 | Active-low parallel load | PC6 / CN10.4 |
| 5 | HC165 QH | PB14 / CN10.28 |
| 6 | GND | CN10.20 |

The input PCB runs only at **3.3 V**. Its sixteen-pin J2 has input A–H
on odd pins and ground on even pins. Fit a shunt across each input/ground
pair to read zero; remove it to read one through the 10 kΩ pull-up.
A maps to process bit 0 and H to bit 7. All shunts removed produce 0xFF;
all fitted produce 0x00. The firmware scans the HC165 at 1 kHz.

## Input PCB manufacture and assembly

Fabricate two copies of the supplied **50 × 40 × 1.6 mm**, two-layer board.
Use the checked-in Gerber job and drill, including the NPTH mounting drills.
The four Ø3.2 mm mounting centres are (4,4), (46,4), (4,36), (46,36) mm.
The project requires 0.20 mm electrical clearance, 0.25 mm minimum track
width, 0.60/0.30 mm minimum via diameter/drill and 0.50 mm copper-to-edge
clearance. No DRC exclusions are configured.

Fit the two capacitors and eight pull-up resistors first. Fit U1 with its
pin 1 at the marked notch end, then J1 and J2 with the marked pin 1
orientation. U1 is soldered directly to the DIP footprint; an unmodelled
IC socket changes the mechanical envelope and is not part of this BOM.
Inspect soldering and test 3.3 V/GND continuity before plugging in the
Nucleo harness. The populated STEP contains purchased component models;
the board's fit in the full station remains a separate assembly check.

## Build and flash

Use GNU Arm Embedded GCC 13.2.1 or a compatible Cortex-M4 hard-float
toolchain, Python 3, Git and Make. The optional host protocol test requires
CMocka development headers/library (for example, libcmocka-dev). The reviewed binaries and compiler
receipt are under `firmware/release/` and `evidence/physical-build.json`.
Dependencies are fetched at exact public revisions, with unchanged source
checks before each build.

From this package directory:

```sh
python3 firmware/master/fetch-deps.py
make -C firmware/master -j2
make -C firmware/device -j2
make -C firmware/master test
python3 firmware/tests/run-protocol-profile.py
```

The master and device Makefiles use the ST NUCLEO-L476RG startup, linker
script, CMSIS and HAL from STM32CubeL4 v1.18.2. The device stack pin includes
the reviewed response-start timing and fixed-baud recovery changes in
[iolinki PR55](https://github.com/w1ne/iolinki/pull/55) and
[PR56](https://github.com/w1ne/iolinki/pull/56). It keeps timing enforcement
enabled. The master stack is the exact vendored source from the recorded
labwired-core revision. The manifest distinguishes source revisions from
merge/release status.

With one intended ST-LINK connected at a time, a standard OpenOCD install
with ST-LINK and STM32L4 support can program and verify the selected ELF:

```sh
openocd -f interface/stlink.cfg -f target/stm32l4x.cfg \
  -c "program firmware/master/build/iolink-master.elf verify reset exit"
openocd -f interface/stlink.cfg -f target/stm32l4x.cfg \
  -c "program firmware/device/build/iolink-device.elf verify reset exit"
```

Repeat the device operation for the second device. These commands are
reproduction instructions; no physical flashing receipt is included.

## Firmware behaviour and acceptance

The master reads current status first, then initializes all seven writable
L6360 registers with an atomic sequential write while outputs are disabled.
It compares stored parity with the bytes sent, and checks defined register
bits separately from unused reset/read bits. The [repair receipt and red/green
tests](evidence/master-stored-parity/receipt.json) preserve the original
startup failure. The master then selects push-pull, controls
L+ and C/Q, generates an 80 µs wake pulse with timer outputs, waits the
enable/test guard and runs both COM2 ports. It uses fresh clock samples
for each port. NACK, parity, register mismatch and severe PHY faults disable
the affected outputs and latch a diagnostic. The physical device uses an
IRQ receive queue, waits for transmit complete before releasing C/Q, and
records the last request/reply boundary. Its timing quality is explicitly
**ESTIMATED** because IRQ/software timestamps are not a C/Q hardware capture.

Observe `g_master_state[2]`, `g_master_pd[2]`, `g_master_tick_result[2]`
and `g_startup_error` in the master ELF. On each device observe
`g_device_state`, `g_device_pd`, `g_phy_error`, `g_uart_errors`,
`g_rx_overflows`, `g_wake_events` and `g_tx_deadline_errors`.
Set different input shunts on the two boards and confirm independent
process bytes. The image's unassigned bench identity is vendor **0xFFFF**,
device **0x000001**, product **L476-L6362A-DI8**. The full 96-bit MCU UID
is encoded into a sixteen-character serial number.

The recorded checks cover eighteen L6360 host cases, analytical I2C/wake
bounds, 38 shared-stack CTest targets (including response timing and fixed-baud
recovery), four TYPE_2_1 byte profiles, both cross-builds, the device
description and native input PCB checks. The byte-profile fixture disables
its timing gate because it has no timed electrical PHY; the physical image
keeps timing enforcement enabled. They do not establish
physical start-bit delay, wake amplitude/duration, C/Q bitrate, current
limiting, thermal behaviour, cable noise immunity or device conformity.
Before a physical release, capture both ports' wake and request/reply
waveforms, measure the clock/rate under the supported conditions, exercise
disconnect/re-wake and fault recovery, and record independent process data.
The mechanical package must also pass the fitted assembly review.

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
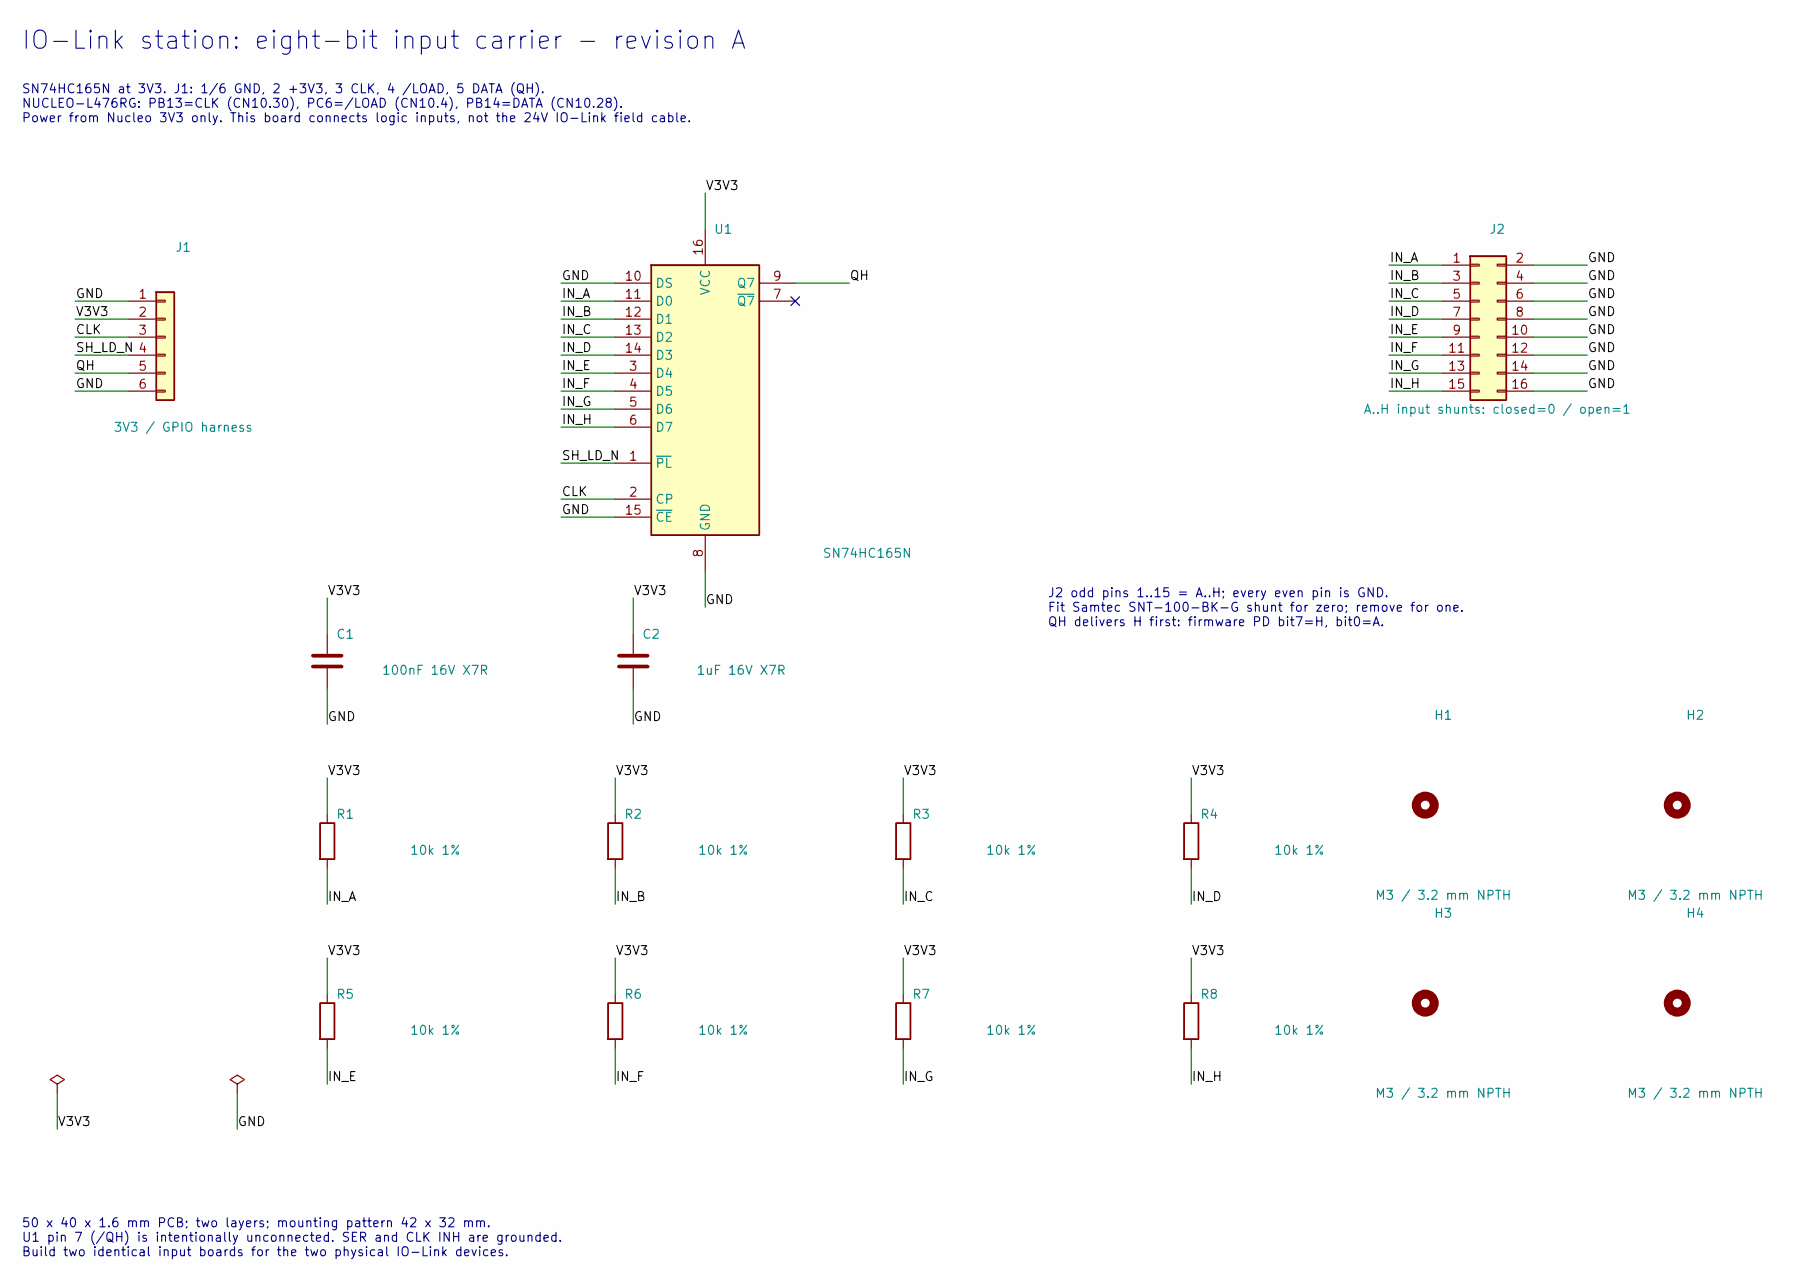
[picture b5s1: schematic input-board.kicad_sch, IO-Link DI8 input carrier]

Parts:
C1: 100nF 16V X7R; C; MPN GRM188R71C104KA01D
C2: 1uF 16V X7R; C; MPN GRM188R71C105KA12D
H1, H2, H3, H4: M3 / 3.2 mm NPTH; MountingHole
J1: 3V3 / GPIO harness; MCU6; MPN B6B-XH-A(LF)(SN)
J2: A..H input shunts: closed=0 / open=1; INPUT16; MPN TSW-108-07-G-D
R1, R2, R3, R4, R5, R6, R7, R8: 10k 1%; R; MPN ERJ-6ENF1002V
U1: SN74HC165N; U; MPN SN74HC165N

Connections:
/CLK: J1.3, U1.2 (CP)
/GND: C1.2, C2.2, J1.1, J1.6, J2.2, J2.4, J2.6, J2.8, J2.10, J2.12, J2.14, J2.16, U1.8 (GND), U1.10 (DS), U1.15 (~CE)
/IN_A: J2.1, R1.2, U1.11 (D0)
/IN_B: J2.3, R2.2, U1.12 (D1)
/IN_C: J2.5, R3.2, U1.13 (D2)
/IN_D: J2.7, R4.2, U1.14 (D3)
/IN_E: J2.9, R5.2, U1.3 (D4)
/IN_F: J2.11, R6.2, U1.4 (D5)
/IN_G: J2.13, R7.2, U1.5 (D6)
/IN_H: J2.15, R8.2, U1.6 (D7)
/QH: J1.5, U1.9 (Q7)
/SH_LD_N: J1.4, U1.1 (~PL)
/V3V3: C1.1, C2.1, J1.2, R1.1, R2.1, R3.1, R4.1, R5.1, R6.1, R7.1, R8.1, U1.16 (VCC)

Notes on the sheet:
IO-Link station: eight-bit input carrier - revision A
SN74HC165N at 3V3. J1: 1/6 GND, 2 +3V3, 3 CLK, 4 /LOAD, 5 DATA (QH). NUCLEO-L476RG: PB13=CLK (CN10.30), PC6=/LOAD (CN10.4), PB14=DATA (CN10.28). Power from Nucleo 3V3 only. This board connects logic inputs, not the 24V IO-Link field cable.
J2 odd pins 1..15 = A..H; every even pin is GND. Fit Samtec SNT-100-BK-G shunt for zero; remove for one. QH delivers H first: firmware PD bit7=H, bit0=A.
50 x 40 x 1.6 mm PCB; two layers; mounting pattern 42 x 32 mm. U1 pin 7 (/QH) is intentionally unconnected. SER and CLK INH are grounded. Build two identical input boards for the two physical IO-Link devices.

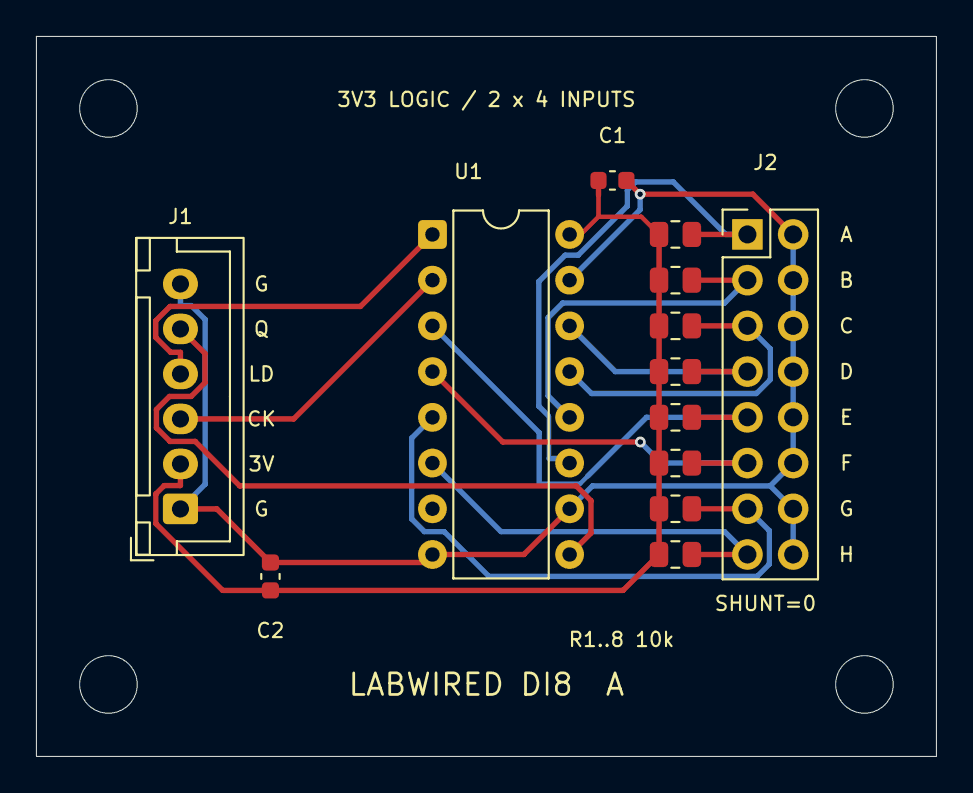
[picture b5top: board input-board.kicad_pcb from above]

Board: 2 copper layers, 50.0 x 40.0 mm, 17 parts (0 on the bottom side), 13 nets.
